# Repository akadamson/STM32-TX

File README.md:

# STM32-TX - Integration of STM32 and a couple of Radio chipsets

#### NOTICE: Non-functional at the moment, work in process ####

20130821 - beginning schematic capture - ADF7012 is pretty much complete on the radio side 
         - Note this is a VHF implementation at the moment with the final filter components, etc.

20131201 - added SIradio directory with v0.1 4464 radio.  Notes: is 3v3 only but could work on a pro-mini if 3v3 version.  Laid our for STM32-MiniF3 as a daughter card mate (sandwich).  This version is 144mhz version

20131204 - updates SIradio with v0.2 4464 radio version… Nothing significant, just fixed some trace widths, some routing and added some silkscreen to the bottom of the board… Still working on final version ready for a board build.

20131205 - changed the VCXO to the *tiny* version and verified the footprint (which was wrong prior :( ).

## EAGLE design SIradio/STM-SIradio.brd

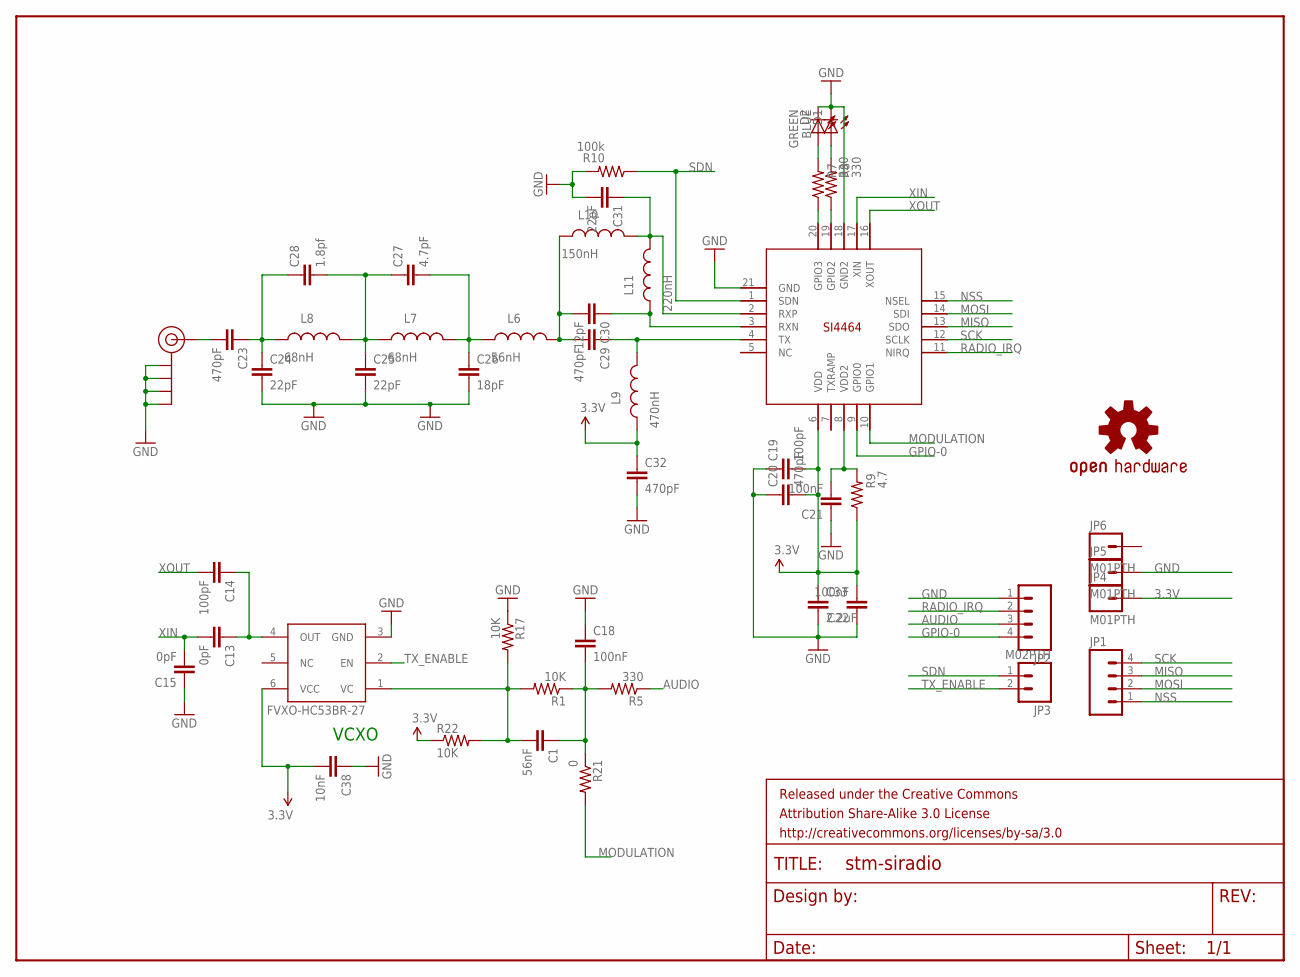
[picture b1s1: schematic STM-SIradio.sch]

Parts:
C1: 56nF; 0603-CAP
C13, C15: 0pF; 0603-CAP
C14, C19: 100pF; 0603-CAP
C18, C21, C22: 100nF; 0603-CAP
C20, C23, C29, C32: 470pF; 0603-CAP
C24, C25, C31: 22pF; 0603-CAP
C26: 18pF; 0603-CAP
C27: 4.7pF; 0603-CAP
C28: 1.8pf; 0603-CAP
C30: 12pF; 0603-CAP
C33: 2.2uF; 1206
C38: 10nF; 0603-CAP
D1: BLUE; LED-0603
D2: GREEN; LED-0603
FRAME1: FRAME-LETTER; CREATIVE_COMMONS
FVXO-HC53BR-27: VCXO-SMDSMD3X; VCXO-SMD-5X3.2
J$2: SMA_EDGE; SMA-EDGE
JP1, JP2: M04PTH; 1X04
JP3: M02PTH; 1X02
JP4, JP5, JP6: M01PTH; 1X01
L6: 56nH; 0603
L7, L8: 68nH; 0603
L9: 470nH; 0603
L10: 150nH; 0603
L11: 220nH; 0603
LOGO1: OSHW-LOGOL; OSHW-LOGO-L
R1, R17, R22: 10K; 0603-RES
R5, R7, R8: 330; 0603-RES
R9: 4.7; 0603-RES
R10: 100k; 0603-RES
R21: 0; 0603-RES
U$3: SI4464; QFN20+GNDPAD

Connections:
3.3V: C19.2, C20.2, C22.2, C32.1, C33.1, C38.2, FVXO-HC53BR-27.6 (VCC), JP4.1, L9.1, R9.1, R22.1, U$3.6 (VDD)
AUDIO: JP2.3, R5.1
GND: C15.1, C18.1, C19.1, C20.1, C21.1, C22.1, C24.2, C25.2, C26.2, C31.2, C32.2, C33.2, C38.1, D1.C, D2.C, FVXO-HC53BR-27.3 (GND), J$2.GND@0 (GND), J$2.GND@1 (GND), J$2.GND@2 (GND), J$2.GND@3 (GND), JP2.1, JP5.1, R10.2, R17.1, U$3.18 (GND2), U$3.21 (GND)
GPIO-0: JP2.4, U$3.9 (GPIO0)
MISO: JP1.3, U$3.13 (SDO)
MODULATION: R21.2, U$3.10 (GPIO1)
MOSI: JP1.2, U$3.14 (SDI)
unnamed: C1.2, FVXO-HC53BR-27.1 (VC), R1.2, R17.2, R22.2
unnamed: C1.1, C18.2, R1.1, R5.2, R21.1
unnamed: C13.1, C14.1, FVXO-HC53BR-27.4 (OUT)
unnamed: C23.2, J$2.SIG (SIGNAL)
unnamed: C23.1, C24.1, C28.1, L8.1
unnamed: C25.1, C27.1, C28.2, L7.1, L8.2
unnamed: C26.1, C27.2, L6.1, L7.2
unnamed: C29.1, L9.2, U$3.4 (TX)
unnamed: C29.2, C30.2, L6.2, L10.1
unnamed: C30.1, L11.1, U$3.3 (RXN)
unnamed: C31.1, L10.2, L11.2, U$3.2 (RXP)
unnamed: D1.A, R8.2
unnamed: D2.A, R7.2
unnamed: R7.1, U$3.20 (GPIO3)
unnamed: R8.1, U$3.19 (GPIO2)
unnamed: C21.2, R9.2, U$3.8 (VDD2)
NSS: JP1.1, U$3.15 (NSEL)
RADIO_IRQ: JP2.2, U$3.11 (NIRQ)
SCK: JP1.4, U$3.12 (SCLK)
SDN: JP3.1, R10.1, U$3.1 (SDN)
TX_ENABLE: FVXO-HC53BR-27.2 (EN), JP3.2
XIN: C13.2, C15.2, U$3.17 (XIN)
XOUT: C14.2, U$3.16 (XOUT)

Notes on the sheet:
VCXO

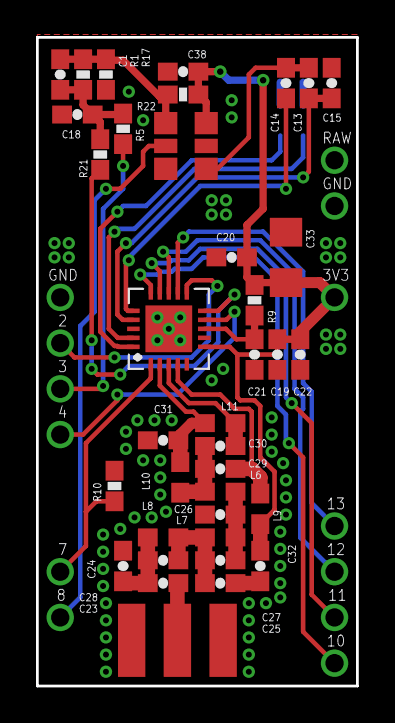
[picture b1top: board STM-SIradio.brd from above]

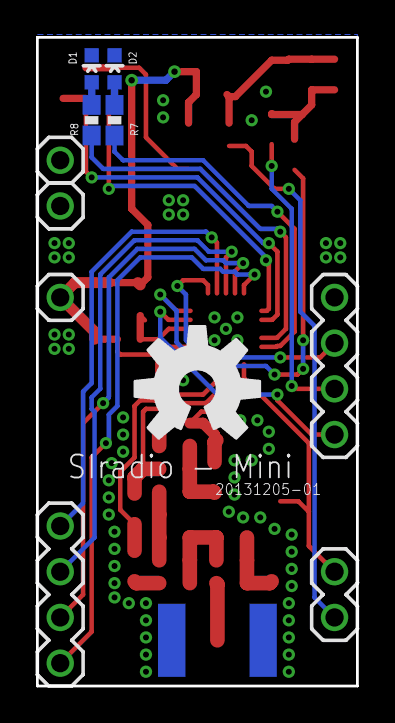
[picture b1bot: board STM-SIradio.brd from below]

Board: 2 copper layers, 17.8 x 36.0 mm, 49 parts (11 on the bottom side), 30 nets.

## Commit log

2013-11-20 work in process
2013-12-02 updated for SIradio version in noted directory
2013-12-04 updated with v0.2 - see Readme for details
2013-12-05 few more tweaks
2013-12-06 Updated with new VCXO footprint, seen readme for other specifics
2013-12-13 updated silkscreen on SIradio
2013-12-22 First Version - PCB produced

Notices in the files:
parts and their libraries:
SparkFun-Aesthetics: Licensing: CC v3.0 Share-Alike You are welcome to use this library for commercial purposes.
SparkFun-Aesthetics: Released under the Creative Commons Attribution Share-Alike 3.0 License
SparkFun-Aesthetics: http://creativecommons.org/licenses/by-sa/3.0
